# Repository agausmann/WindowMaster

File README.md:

# WindowMaster

A physical controller for the Windows Volume Mixer (sndvol).

This project is made up of multiple hardware and software parts:

- `pcb/` - KiCad design files for the controller PCB.

- `case/` - A laser-cut acrylic case for the PCB.

- `firmware/` - Firmware running on the controller.

- `host-controller/` (**WIP**) - PC software to bridge between the controller
  and the system volume mixer.

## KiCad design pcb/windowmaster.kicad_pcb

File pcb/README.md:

# WindowMaster PCB

This circuit board is the main board for the WindowMaster physcial controller.
It supports 6 control channels which can be individually assigned to different
channels via the WindowMaster software.

The MCU powering this board is an [STM32F072C8], which can read the encoder
states and set indicators via GPIO, and communicate with the host computer over
USB. You can flash the provided firmware to communicate with and control the
WindowMaster host software, or write and flash your own if you have another
usecase for the control surface. (In the future, I may provide other firmwares
to turn it into a generic input device like a joystick or MIDI. Feel free to
contact me if you'd like to commission a custom firmware - I'd love to hear
about your idea!)

This board is developed with KiCad version 5.1.9. Components, especially those
that can or must be surface-mounted, are picked from the [JLCPCB SMT Parts
Library](https://jlcpcb.com/parts), if there is a suitable part there. This
makes it more convenient to fabricate and assemble, as they will do most of the
work. Everything else is picked to be easy to hand-solder with an iron, which
generally means through-hole or large tabs.

## Ordering

TODO

## Programming Reference & Pinout

The PCB is laid out into six channels. Each channel has its own quadrature
encoder (PEC11R), a pushbutton switch (built into the encoder), and an
indicator LED. These peripherals are controlled by the onboard [STM32F072C8]
microcontroller, which is also given a USB port so it can communicate with a
host system.

Here is the pinout of the STM32 chip to all of its connected peripherals, for
quick reference while programming:

| Physical | Logical | Description          | Direction | Logic      |
|----------|---------|----------------------|-----------|------------|
| 25       | PB12    | Status LED           | Output    | Active Low |
| 32       | PA11    | USB D-               |           |            |
| 33       | PA12    | USB D+               |           |            |
| 3        | PC14    | Channel 1 Encoder A  | Input     | Active Low |
| 2        | PC13    | Channel 1 Encoder B  | Input     | Active Low |
| 39       | PB3     | Channel 1 Pushbutton | Input     | Active Low |
| 40       | PB4     | Channel 1 Indicator  | Output    | Active Low |
| 46       | PB9     | Channel 2 Encoder A  | Input     | Active Low |
| 45       | PB8     | Channel 2 Encoder B  | Input     | Active Low |
| 38       | PA15    | Channel 2 Pushbutton | Input     | Active Low |
| 41       | PB5     | Channel 2 Indicator  | Output    | Active Low |
| 43       | PB7     | Channel 3 Encoder A  | Input     | Active Low |
| 42       | PB6     | Channel 3 Encoder B  | Input     | Active Low |
| 27       | PB14    | Channel 3 Pushbutton | Input     | Active Low |
| 28       | PB15    | Channel 3 Indicator  | Output    | Active Low |
| 18       | PB0     | Channel 4 Encoder A  | Input     | Active Low |
| 17       | PA7     | Channel 4 Encoder B  | Input     | Active Low |
| 6        | PF1     | Channel 4 Pushbutton | Input     | Active Low |
| 10       | PA0     | Channel 4 Indicator  | Output    | Active Low |
| 16       | PA6     | Channel 5 Encoder A  | Input     | Active Low |
| 15       | PA5     | Channel 5 Encoder B  | Input     | Active Low |
| 5        | PF0     | Channel 5 Pushbutton | Input     | Active Low |
| 11       | PA1     | Channel 5 Indicator  | Output    | Active Low |
| 14       | PA4     | Channel 6 Encoder A  | Input     | Active Low |
| 13       | PA3     | Channel 6 Encoder B  | Input     | Active Low |
| 4        | PC15    | Channel 6 Pushbutton | Input     | Active Low |
| 12       | PA2     | Channel 6 Indicator  | Output    | Active Low |

## Flashing

The focus of this section will be on the specifics of flashing on this board. I
expect the reader to know generally how to program STM32 devices; there's plenty
of other resources on the Internet that explain it better than I ever could.

There are two ways that the STM32 chip can be flashed: the USB DFU protocol,
and the ST-Link debug interface.

### USB DFU

To start the device in DFU mode:  While holding down the DFU button, connect
the USB cable so that it powers on and connects to the computer. Once it has
turned on, you can let go of DFU.

(_Note_: If the device is already connected, you can enter DFU mode without
disconnecting by holding down DFU and pressing and releasing RESET. Again, you
can release DFU once it has reset.)

Once the device is in DFU mode, you can use a tool like [DfuSe] or [dfu-util] on
the host computer to connect to the device and flash firmware binaries.

### ST-Link

There is a spot for an ST-Link / SWD breakout header at the top of the PCB, in
between the reset switch and USB port. The pinout of that port is designed to
match the SWD header on Discovery/Nucleo boards, so from left to right:

1. 3v3 power (not connected in rev1, you have to supply power over USB)
2. SWCLK
3. GND
4. SWDIO
5. NRST
6. Not connected (normally SWO, which is unsupported by this chip).

Connect an ST-Link to that header, and connect both the ST-Link and the PCB to
the computer via USB. Then you can flash using whatever ST-Link compatible tool
or method you prefer. (openOCD, cargo-flash, etc)

[STM32F072C8]: https://www.st.com/en/microcontrollers-microprocessors/stm32f072c8.html
[DfuSe]: https://www.st.com/en/development-tools/stsw-stm32080.html#overview
[dfu-util]: http://dfu-util.sourceforge.net/

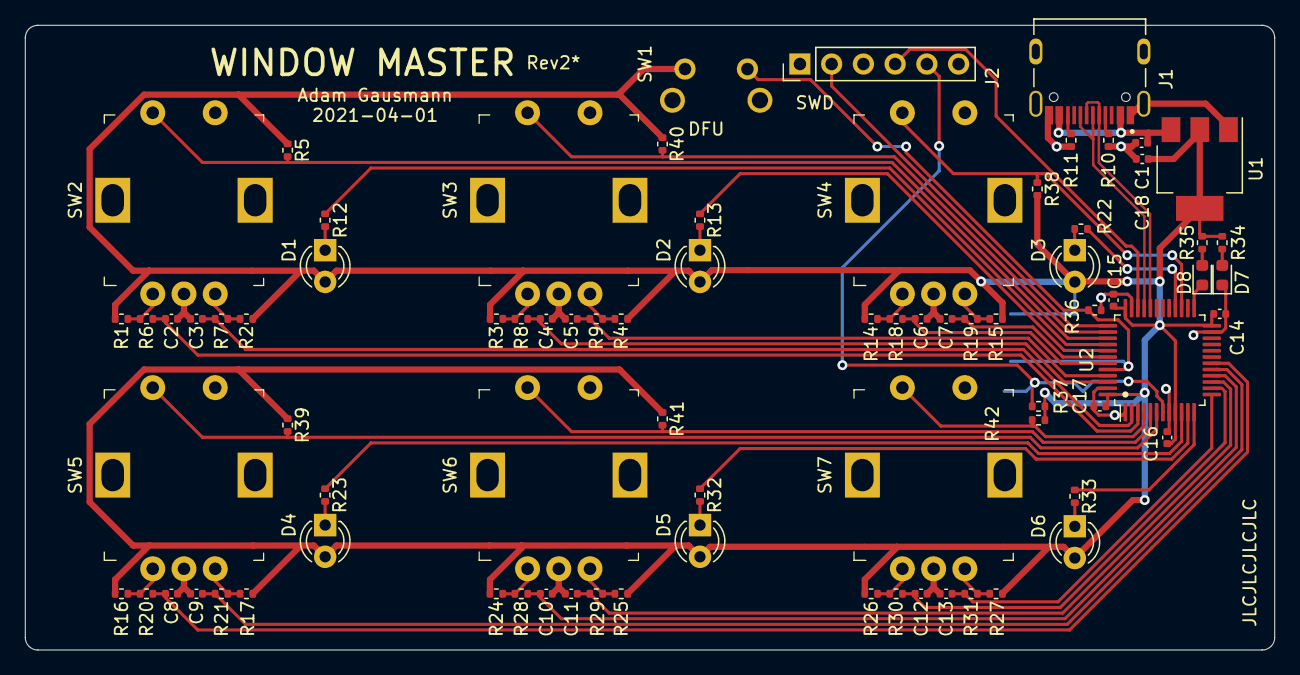
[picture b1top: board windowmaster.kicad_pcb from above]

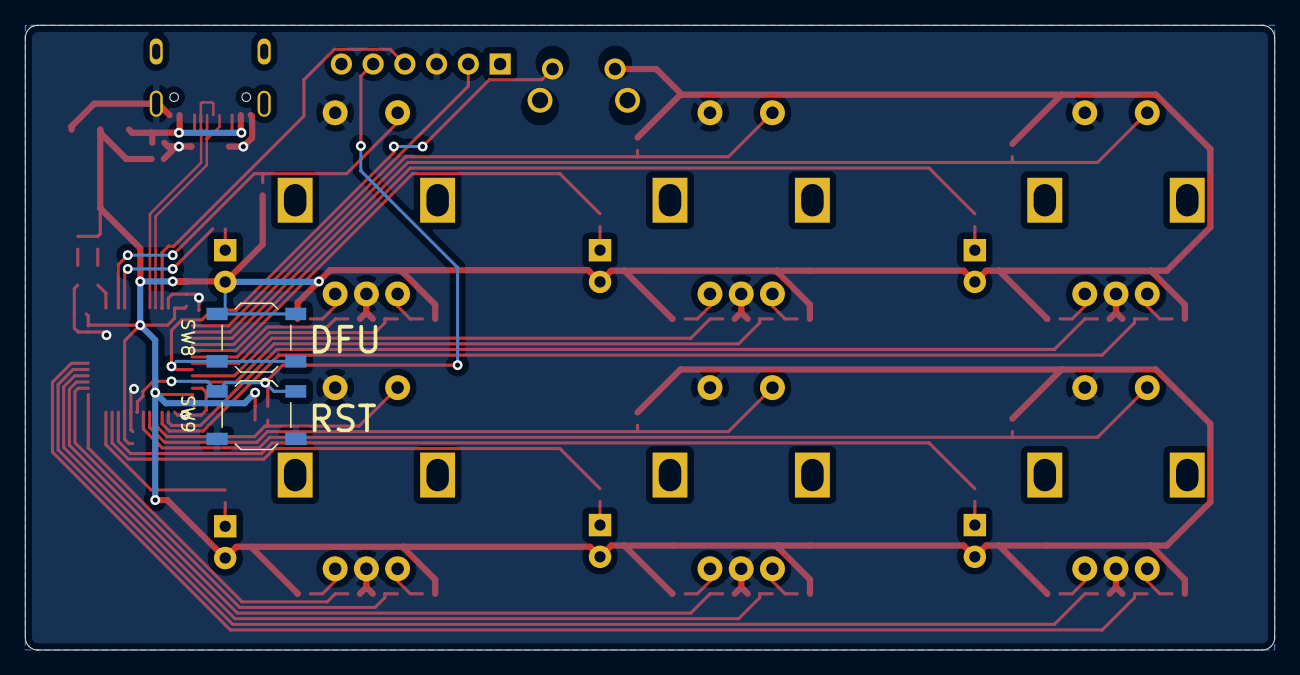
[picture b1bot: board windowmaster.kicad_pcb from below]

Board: 2 copper layers, 100.0 x 50.0 mm, 81 parts (2 on the bottom side), 56 nets.

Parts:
C1, C18: 4.7uF; C_0402_1005Metric
C2, C3, C4, C5, C6, C7, C8, C9, C10, C11, C12, C13: 10nF; C_0402_1005Metric
C14, C15, C16, C17: 100nF; C_0402_1005Metric
D1, D2, D3, D4, D5, D6: LED; LED_D3.0mm
D7: PWR_LED; LED_0603_1608Metric
D8: STATUS_LED; LED_0603_1608Metric
J1: USB_C_Receptacle_USB2.0; HRO_TYPE-C-31-M-12
J2: SWD; PinHeader_1x06_P2.54mm_Vertical
R1, R2, R3, R4, R5, R6, R7, R8, R9, R14, R15, R16, R17, R18, R19, R20, R21, R24, R25, R26, R27, R28, R29, R30, R31, R36, R37, R38, R39, R40, R41, R42: 10K; R_0402_1005Metric
R10, R11: 5.1K; R_0402_1005Metric
R12, R13, R22, R23, R32, R33, R34, R35: 1K; R_0402_1005Metric
SW1: SW_DFU2; MJTP1117
SW2, SW3, SW4, SW5, SW6, SW7: ENC; Rotary_Encoder_Switched_PEC11R
SW8: SW_DFU; SW_SPST_TL3342
SW9: SW_RST; SW_SPST_TL3342
U1: AZ1117-3.3; SOT-223-3_TabPin2
U2: STM32F072C8T6; LQFP-48_7x7mm_P0.5mm

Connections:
+3V3: C14.1, C15.1, C16.1, C17.1, C18.1, D1.2, D2.2, D3.2, D4.2, D5.2, D6.2, R1.1, R2.1, R3.1, R4.1, R5.1, R14.1, R15.1, R16.1, R17.1, R24.1, R25.1, R26.1, R27.1, R34.1, R35.1, R37.1, R38.1, R39.1, R40.1, R41.1, R42.1, SW1.2, SW8.1, U1.2, U2.9, U2.24, U2.36, U2.48
DFU: R36.1, SW1.1, SW8.2, U2.44
ENC_1A: C2.1, R6.2, U2.3
ENC_1B: C3.1, R7.2, U2.2
ENC_2A: C4.1, R8.2, U2.46
ENC_2B: C5.1, R9.2, U2.45
ENC_3A: C6.1, R18.2, U2.43
ENC_3B: C7.1, R19.2, U2.42
ENC_4A: C8.1, R20.2, U2.18
ENC_4B: C9.1, R21.2, U2.17
ENC_5A: C10.1, R28.2, U2.16
ENC_5B: C11.1, R29.2, U2.15
ENC_6A: C12.1, R30.2, U2.14
ENC_6B: C13.1, R31.2, U2.13
GND: C1.2, C2.2, C3.2, C4.2, C5.2, C6.2, C7.2, C8.2, C9.2, C10.2, C11.2, C12.2, C13.2, C14.2, C15.2, C16.2, C17.2, C18.2, D7.1, J1.A1, J1.A12, J1.B1, J1.B12, J1.S1, J2.3, R10.1, R11.1, R36.2, SW2.C, SW2.S2, SW3.C, SW3.S2, SW4.C, SW4.S2, SW5.C, SW5.S2, SW6.C, SW6.S2, SW7.C, SW7.S2, SW9.2, U1.1, U2.1, U2.8, U2.23, U2.35, U2.47
IND_1: R12.1, U2.40
IND_2: R13.1, U2.41
IND_3: R22.1, U2.28
IND_4: R23.1, U2.10
IND_5: R32.1, U2.11
IND_6: R33.1, U2.12
NRST: J2.5, R37.2, SW9.1, U2.7
unnamed: D1.1, R12.2
unnamed: D2.1, R13.2
unnamed: D3.1, R22.2
unnamed: D4.1, R23.2
unnamed: D5.1, R32.2
unnamed: D6.1, R33.2
unnamed: D7.2, R34.2
unnamed: D8.2, R35.2
unnamed: J1.A5, R10.2
unnamed: J1.B5, R11.2
unnamed: R1.2, R6.1, SW2.A
unnamed: R2.2, R7.1, SW2.B
unnamed: R3.2, R8.1, SW3.A
unnamed: R4.2, R9.1, SW3.B
unnamed: R14.2, R18.1, SW4.A
unnamed: R15.2, R19.1, SW4.B
unnamed: R16.2, R20.1, SW5.A
unnamed: R17.2, R21.1, SW5.B
unnamed: R24.2, R28.1, SW6.A
unnamed: R25.2, R29.1, SW6.B
unnamed: R26.2, R30.1, SW7.A
unnamed: R27.2, R31.1, SW7.B
STATUS: D8.1, U2.25
SWCLK: J2.2, U2.37
SWDIO: J2.4, U2.34
SW_1: R5.2, SW2.S1, U2.39
SW_2: R40.2, SW3.S1, U2.38
SW_3: R38.2, SW4.S1, U2.27
SW_4: R39.2, SW5.S1, U2.6
SW_5: R41.2, SW6.S1, U2.5
SW_6: R42.2, SW7.S1, U2.4
USB_D+: J1.A6, J1.B6, U2.33
USB_D-: J1.A7, J1.B7, U2.32
VBUS: C1.1, J1.A4, J1.A9, J1.B4, J1.B9, U1.3

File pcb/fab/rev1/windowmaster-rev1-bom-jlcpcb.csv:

Comment,Designator,Footprint,LCSC Part #
4.7uF,"C1,C18",0402,C23733
10nF,C2-13,0402,C15195
100nF,C14-17,0402,C1525
PWR_LED,D7,0603,C72043
STATUS_LED,D8,0603,C72038
USB_C_Receptacle_USB2.0,J1,,C165948
5.1K,"R10,R11",0402,C25905
1K,"R12, R13, R22, R23, R32-35",0402,C11702
10K,"R1-9, R14-21, R24-31, R36-42",0402,C25744
AZ1117-3.3,U1,SOT-223,C108494
STM32F072C8T6,U2,LQFP-48_7.0x7.0x0.5P,C80488

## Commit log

2021-02-04 Make a subdirectory for PCB design files
2021-02-04 Add READMEs and LICENSEs
2021-02-05 Add relevant part numbers and datasheets to schematic
2021-02-05 Reset silkscreen labels
2021-02-06 Rearrange vias to cut less into ground plane
2021-02-11 Add firmware crate, with runtime and peripheral libraries
2021-02-11 Add build script to detect changes to memory.x
2021-02-11 Add USB device dependencies
2021-02-12 Initialize channels and USB
2021-02-13 Separate the USB/MCU/power supply parts of the schematic
2021-02-16 USB PID registered!
2021-02-16 Optimize for size in debug builds
2021-02-16 Add HID polling and optimize report
2021-02-20 Changes from testing channels and USB on dev board
2021-02-21 Mega refactor to make the system more composable and support different pinouts
2021-02-21 Read LED state from output reports
2021-02-21 Add custom panic handler with LED pattern
2021-02-22 Add reset switch models to PCB and add case draft
2021-02-22 Add switch labels on PCB
2021-03-11 Hierarchical redesign and add ST-Link SWD header
2021-03-11 Add rev1 case files
2021-03-11 Update CAD models and add renders
2021-03-11 Add programming/flashing instructions for PCB
2021-03-11 Rewrap
2021-03-12 Rough PoC of audio device/app enumeration on Windows
2021-03-12 Use VARENUM constants
2021-03-12 Move audio code into a separate module
2021-03-13 Add USB HID device enumeration
2021-03-17 Migrate to Git LFS
2021-03-17 Final changes to PCB before ordering...
    - Add external pull-ups to switch inputs.
    - Double-check and fix LCSC part numbers.
    - Add filter capacitor to regulator output.
2021-03-17 Add fabrication files from rev1 1st run
2021-03-17 Update Rev1 pinout in firmware
2021-03-22 Fix firmware compile error
2021-03-22 Read/write HID reports to devices
2021-03-23 Store device state and translate to/from HID reports
2021-03-31 some comments on panic handling
2021-04-01 Initialize indicators to "off" state as early as possible
    Prevents a momentary blink that used to happen at startup - since the
    LEDs are wired active-low and they start in low state when changed to
    output mode, if they aren't immediately set high, they will be "on"
    until their next update.
2021-04-01 Switch to Rev1 PCB system by default.
    Rev1 PCBs have arrived! So I'll be primarily using them to test instead
    of the Discovery board.
2021-04-01 Add startup sequence to the status LED.
2021-04-01 Fix MJTP1117 footprint
2021-04-01 Add central app manager and device control threads
2021-04-03 Create a more minimal system for the panic handler
2021-09-02 Clean slate
2021-09-04 Add core and Windows backend
2021-09-05 Add HidApi backend
2021-09-05 hid: Prevent crashing when device is disconnected
2021-09-06 Fix crashes in windows audio backend
2021-09-06 Add menus and bindings
2021-09-06 Auto-close menu when selected, and keep channel state synced when rebound
2021-09-06 Fix deadlocks from full channels
2021-09-06 Improve responsiveness of HID backend
    Only handled 1 incoming message before yielding, which severely limited
    thoughput. Now it makes sure the channel is empty before yielding.
2021-09-07 Make notification clients block until events are sent
2021-09-09 windows: Add controls for audio sessions (applications)
2021-09-11 Update windows audio backend to use external win32-coreaudio crate
2021-09-11 Implement a binding that follows the active window
2021-09-12 Replace FreeCAD models with OpenSCAD
2021-09-12 Actually remove FreeCAD model this time
2021-09-12 Add VS Code workspace to gitignore
2021-09-12 Add default device binding
2021-09-12 windows: Implement default audio devices
2021-09-13 Store callback handles so they won't be unregistered.
2021-09-13 Propagate stream state updates for default device bindings
2021-09-13 host-controller: Update README
2022-12-08 Add photo of built device
